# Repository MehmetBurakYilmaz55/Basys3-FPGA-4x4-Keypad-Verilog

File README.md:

# FPGA Tabanlı 4x4 Matris Keypad Sürücüsü ve Özel PCB Tasarımı (Basys 3)
### 🇬🇧 FPGA Based 4x4 Matrix Keypad Driver & Custom PCB Design

---

## 🇹🇷 Proje Hakkında (Turkish)

Bu proje, **Kocaeli Üniversitesi** Elektronik ve Haberleşme Mühendisliği bölümü kapsamında; Digilent Basys 3 FPGA kartı için geliştirilmiş bir 4x4 Matris Keypad sürücüsü ve donanım tasarımını içerir.

Projenin en özgün yanı, standart "Debouncer" modülleri kullanmak yerine, mekanik gürültüleri (bouncing) donanımsal mantıkla çözen **"Freeze & Latch" (Dondur ve Kilitle)** algoritmasının kullanılmasıdır.

### 🚀 Öne Çıkan Özellikler
* **Freeze (Dondurma) Algoritması:** Tarama sırasında herhangi bir sütundan sinyal (`col != 0`) algılandığı anda tarayıcı sayaç dondurulur. Bu sayede tuş basılı olduğu sürece tarama satır değiştiremez ve kararlı bir okuma sağlanır.
* **Özgün PCB Tasarımı:** Keypad donanımı sıfırdan tasarlanmış ve üretilmiştir.
* **Üretime Özel Kılıflar (BenimKutuphanem):** standart kütüphanedeki kılıflar (footprints) alınmış ve ped yüzeyleri manuel olarak genişletilmiştir. Bu sayede lehimleme kolaylığı sağlanmıştır.
  
### 🛠️ PCB Tasarımı ve "BenimKutuphanem" Detayı
Baskı devre kartı (PCB) tasarımı **KiCad** kullanılarak yapılmıştır. Standart kütüphanedeki direnç (1206) ve buton kılıflarının pedleri, asit indirme işleminde erimemesi ve lehimlemenin kolay olması için manuel olarak büyütülmüştür.

Bu özelleştirilmiş kılıflar, projenin `pcb_design/BenimKutuphanem.pretty` klasörü altında toplanmıştır.

### 📂 Klasör Yapısı
* `verilog_codes/` -> Verilog kaynak kodları (`Top_Module`, `Scanner`, `SevenSeg` vb.).
* `pcb_design/` -> KiCad proje dosyaları, şematik, PCB çizimi ve **BenimKutuphanem** klasörü.
* `docs/` -> Devre şeması (PDF), proje raporu ve görseller.

---

## 🇬🇧 Project Description (English)

This repository contains the full **Verilog source code** and **custom PCB design** files for a 4x4 Matrix Keypad project implemented on the Digilent Basys 3 FPGA board, developed at **Kocaeli University**.

The project features a custom-developed **"Freeze & Latch" scanning algorithm** that eliminates the need for traditional debouncer modules by locking the state upon signal detection.

### 🚀 Key Features
* **Freeze Logic:** Unlike standard scanning, the counter instantly stops (freezes) when a column signal is detected. This prevents the scanner from jumping to the next row during micro-second contact bounces, ensuring a stable output.
* **Custom PCB Design:** The hardware is designed from scratch using **KiCad**.
* **DIY-Friendly Footprints:** To facilitate "Toner Transfer" etching and hand-soldering, standard component footprints were modified with significantly **larger pads**.

### 🛠️ PCB Design & Custom Library
Since the board was manufactured using DIY methods, standard library footprints were too small and risky for hand soldering.
* We created a custom library named **"BenimKutuphanem"** (MyLibrary).
* This library includes modified footprints for resistors and tactile switches with enlarged pads to prevent pad lifting during etching.
* The custom library files can be found in `pcb_design/libraries/BenimKutuphanem`.

### ⚙️ Pinout (Pmod Header JB)
| FPGA Pin | Keypad Pin | Direction |
|----------|------------|-----------|
| JB1    | COL 1      | Input     |
| JB2    | COL 2      | Input     |
| JB3    | COL 3      | Input     |
| JB4    | COL 4      | Input     |
| JB7    | ROW 1      | Output    |
| JB8    | ROW 2      | Output    |
| JB9    | ROW 3      | Output    |
| JB10   | ROW 4      | Output    |

---

## 👥 Authors & Acknowledgments / Yazar ve Teşekkür

**Project Team / Proje Ekibi:**
* **Mehmet Burak YILMAZ** - *FPGA Design & Verification & PCB Design*

## 📄 License
This project is open-source and available for educational purposes.

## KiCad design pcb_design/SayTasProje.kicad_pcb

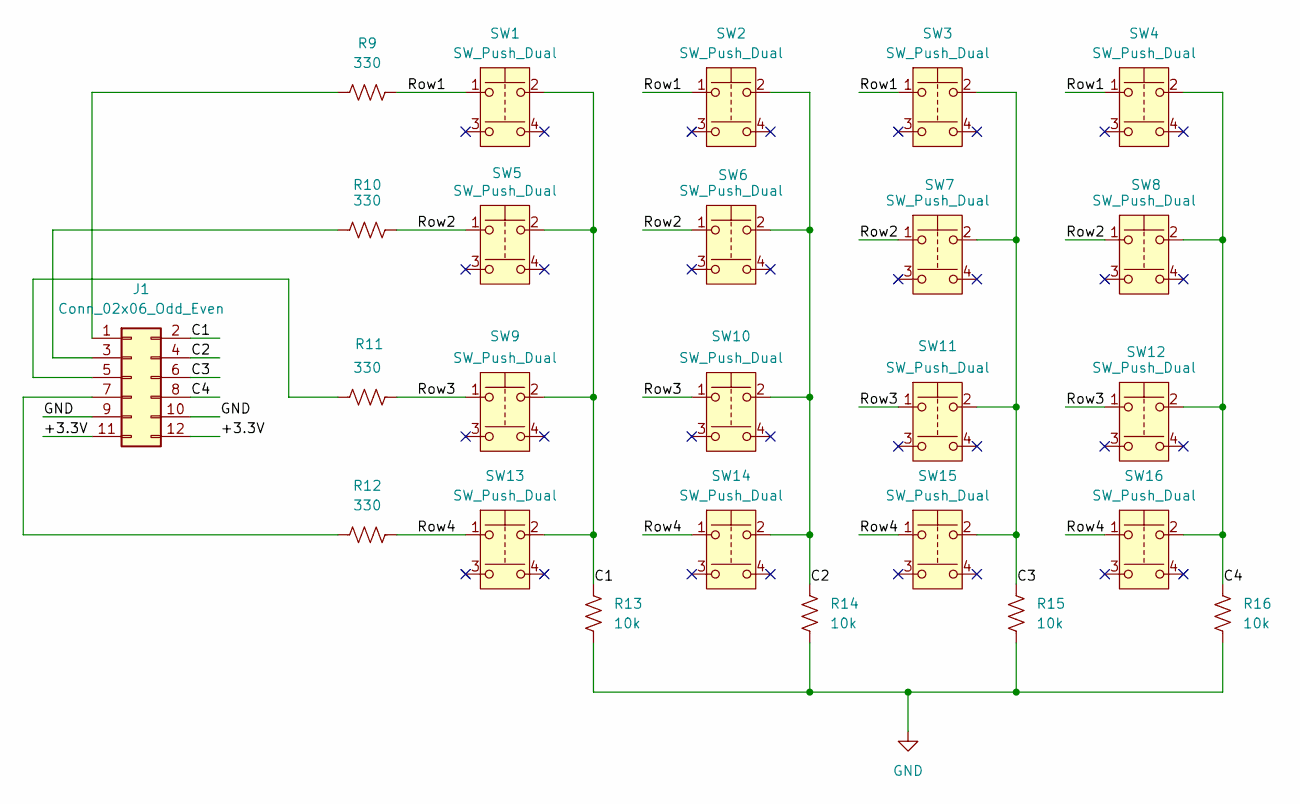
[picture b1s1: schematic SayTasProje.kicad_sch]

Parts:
J1: Conn_02x06_Odd_Even; PinHeader_2x06_P2.54mm_Horizontal
R9, R10, R11, R12: 330; SMD_Res_Big_Pad
R13, R14, R15, R16: 10k; SMD_Res_Big_Pad
SW1, SW2, SW3, SW4, SW5, SW6, SW7, SW8, SW9, SW10, SW11, SW12, SW13, SW14, SW15, SW16: SW_Push_Dual; SW_SPST_PTS645Sx43SMTR92

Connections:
+3.3V: J1.11, J1.12
/C1: J1.2, R13.2, SW1.2, SW5.2, SW9.2, SW13.2
/C2: J1.4, R14.2, SW2.2, SW6.2, SW10.2, SW14.2
/C3: J1.6, R15.2, SW3.2, SW7.2, SW11.2, SW15.2
/C4: J1.8, R16.2, SW4.2, SW8.2, SW12.2, SW16.2
/Row1: R9.2, SW1.1, SW2.1, SW3.1, SW4.1
/Row2: R10.2, SW5.1, SW6.1, SW7.1, SW8.1
/Row3: R11.2, SW9.1, SW10.1, SW11.1, SW12.1
/Row4: R12.2, SW13.1, SW14.1, SW15.1, SW16.1
GND: J1.9, J1.10, R13.1, R14.1, R15.1, R16.1
unnamed: J1.1, R9.1
unnamed: J1.3, R10.1
unnamed: J1.5, R11.1
unnamed: J1.7, R12.1

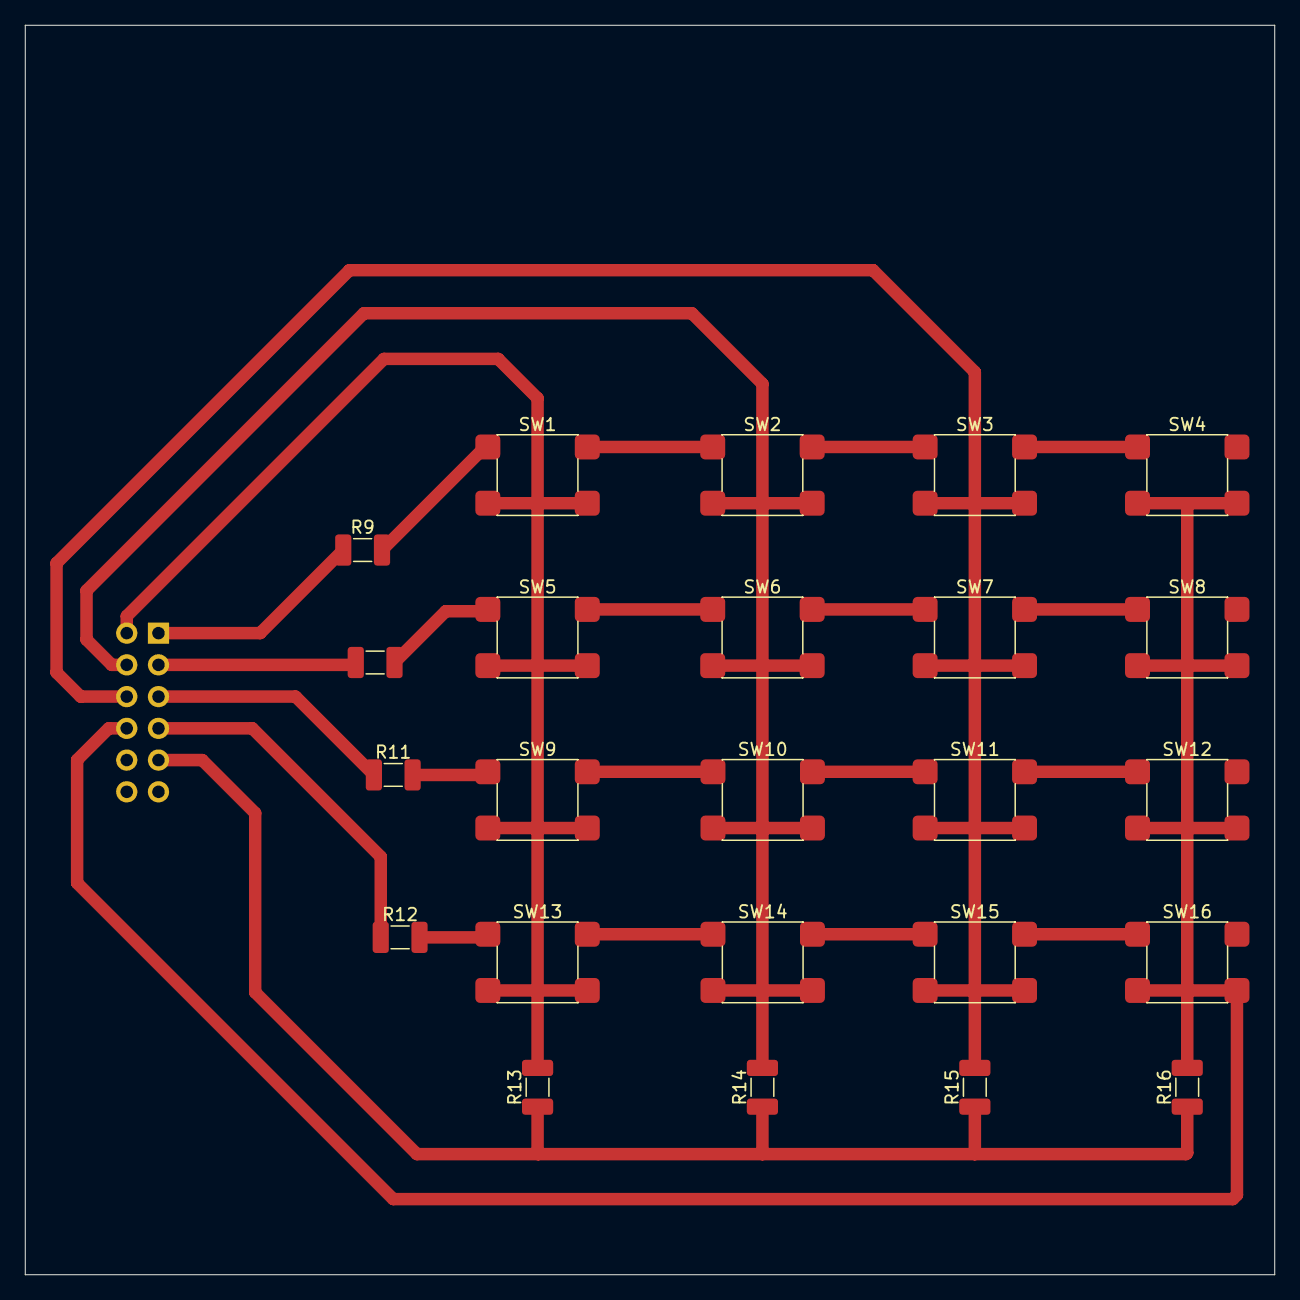
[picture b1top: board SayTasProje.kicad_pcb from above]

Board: 2 copper layers, 100.0 x 100.0 mm, 25 parts (1 on the bottom side), 14 nets.
